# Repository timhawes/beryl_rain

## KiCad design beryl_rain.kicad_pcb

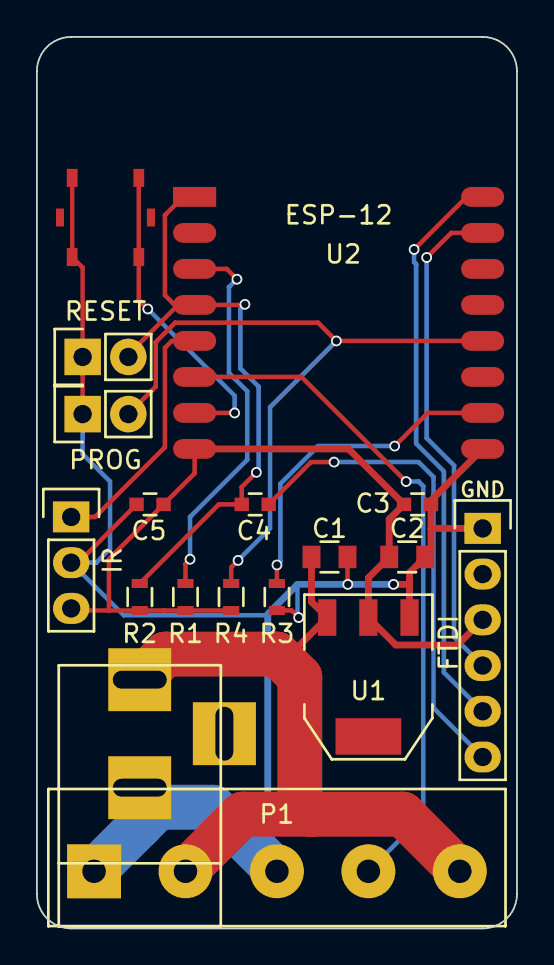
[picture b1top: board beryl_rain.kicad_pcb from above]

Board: 2 copper layers, 26.7 x 49.5 mm, 18 parts (0 on the bottom side), 13 nets.

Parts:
C1, C2: CP; C_0805
C3, C4, C5: 0.1uF; C_0603
CON1: POWER; BARREL_JACK
P1: POWER; Terminal_Block_5.08mm_x5
P2: FTDI; Pin_Header_Straight_1x06
P3: IR; Pin_Header_Straight_1x03
P4: RESET; Pin_Header_Straight_1x02
P5: PROG; Pin_Header_Straight_1x02
R1, R2, R3, R4: 10K; R_0603
SW1: SWITCH; EVQPT5
U1: NCP1117ST33T3G; SOT-223
U2: ESP-12

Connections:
+3V3: C2.1, C3.1, C5.1, P2.3, P3.3, R1.1, R2.1, R4.1, U1.2, U2.8
+5V: C1.1, CON1.1, P1.2, P1.5, U1.3
GND: C1.2, C2.2, C3.2, C5.2, CON1.2, P1.1, P1.3, P2.1, P3.2, P4.1, P5.1, R3.2, SW1.1, U1.1, U2.9
IR_DATA: P3.1, U2.5
LED_DATA: P1.4, U2.6
unnamed: C4.1, P2.6
unnamed: P5.2, R4.2, U2.12
unnamed: R1.2, U2.3
unnamed: R3.1, U2.10
unnamed: SW1.2, U2.7
RESET: C4.2, P4.2, R2.2, U2.1, U2.4
RX: P2.4, U2.15
TX: P2.5, U2.16

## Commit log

2015-11-09 Completed version 1
